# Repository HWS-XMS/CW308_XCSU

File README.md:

Requires JTAG programmer or flash connected to HDS pins to be programmed.
I am using a flash emulator on HDS, i.e. Dediprog EM100.
However, JTAG works equally well.

# Errata and plans for Rev-2:
- Use a different DC supply for VCC INT. This one provides up to 500mA. The chip can draw >500mA is specific scenarios w.r.t. the datasheet.
- Replace the three parallel shunts with my current transformer design
- Connect the SBI signals to the CW308 header, such that chipwhisperer can program (after updating chipwhisperer python, it is currently not supported)

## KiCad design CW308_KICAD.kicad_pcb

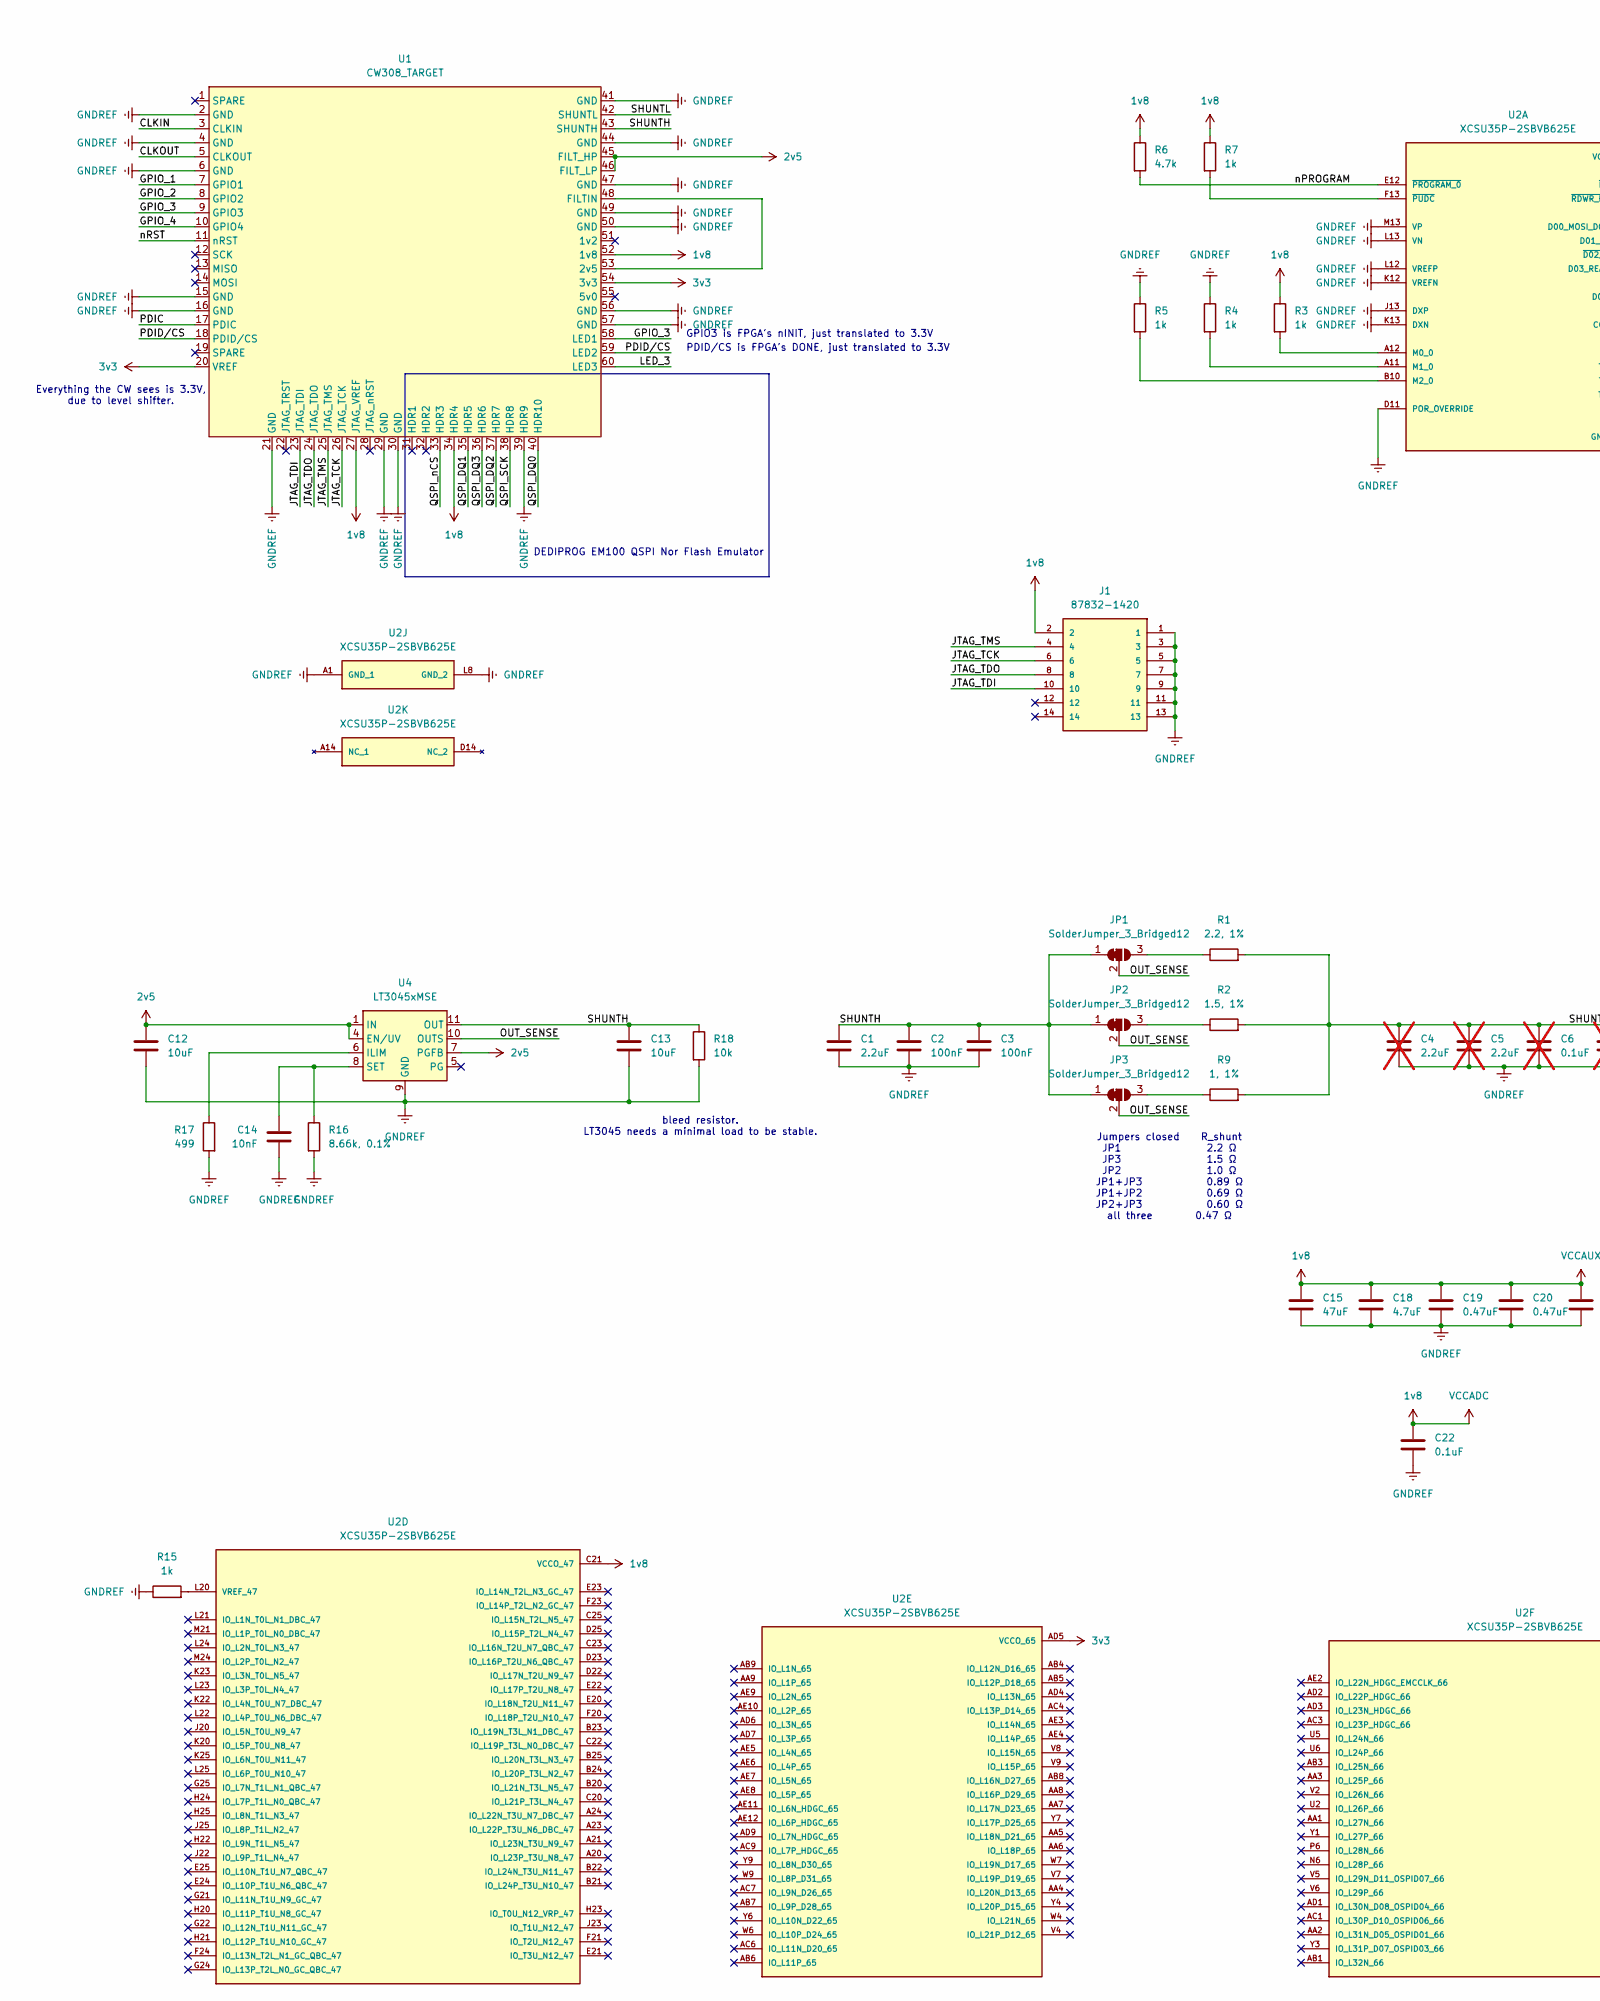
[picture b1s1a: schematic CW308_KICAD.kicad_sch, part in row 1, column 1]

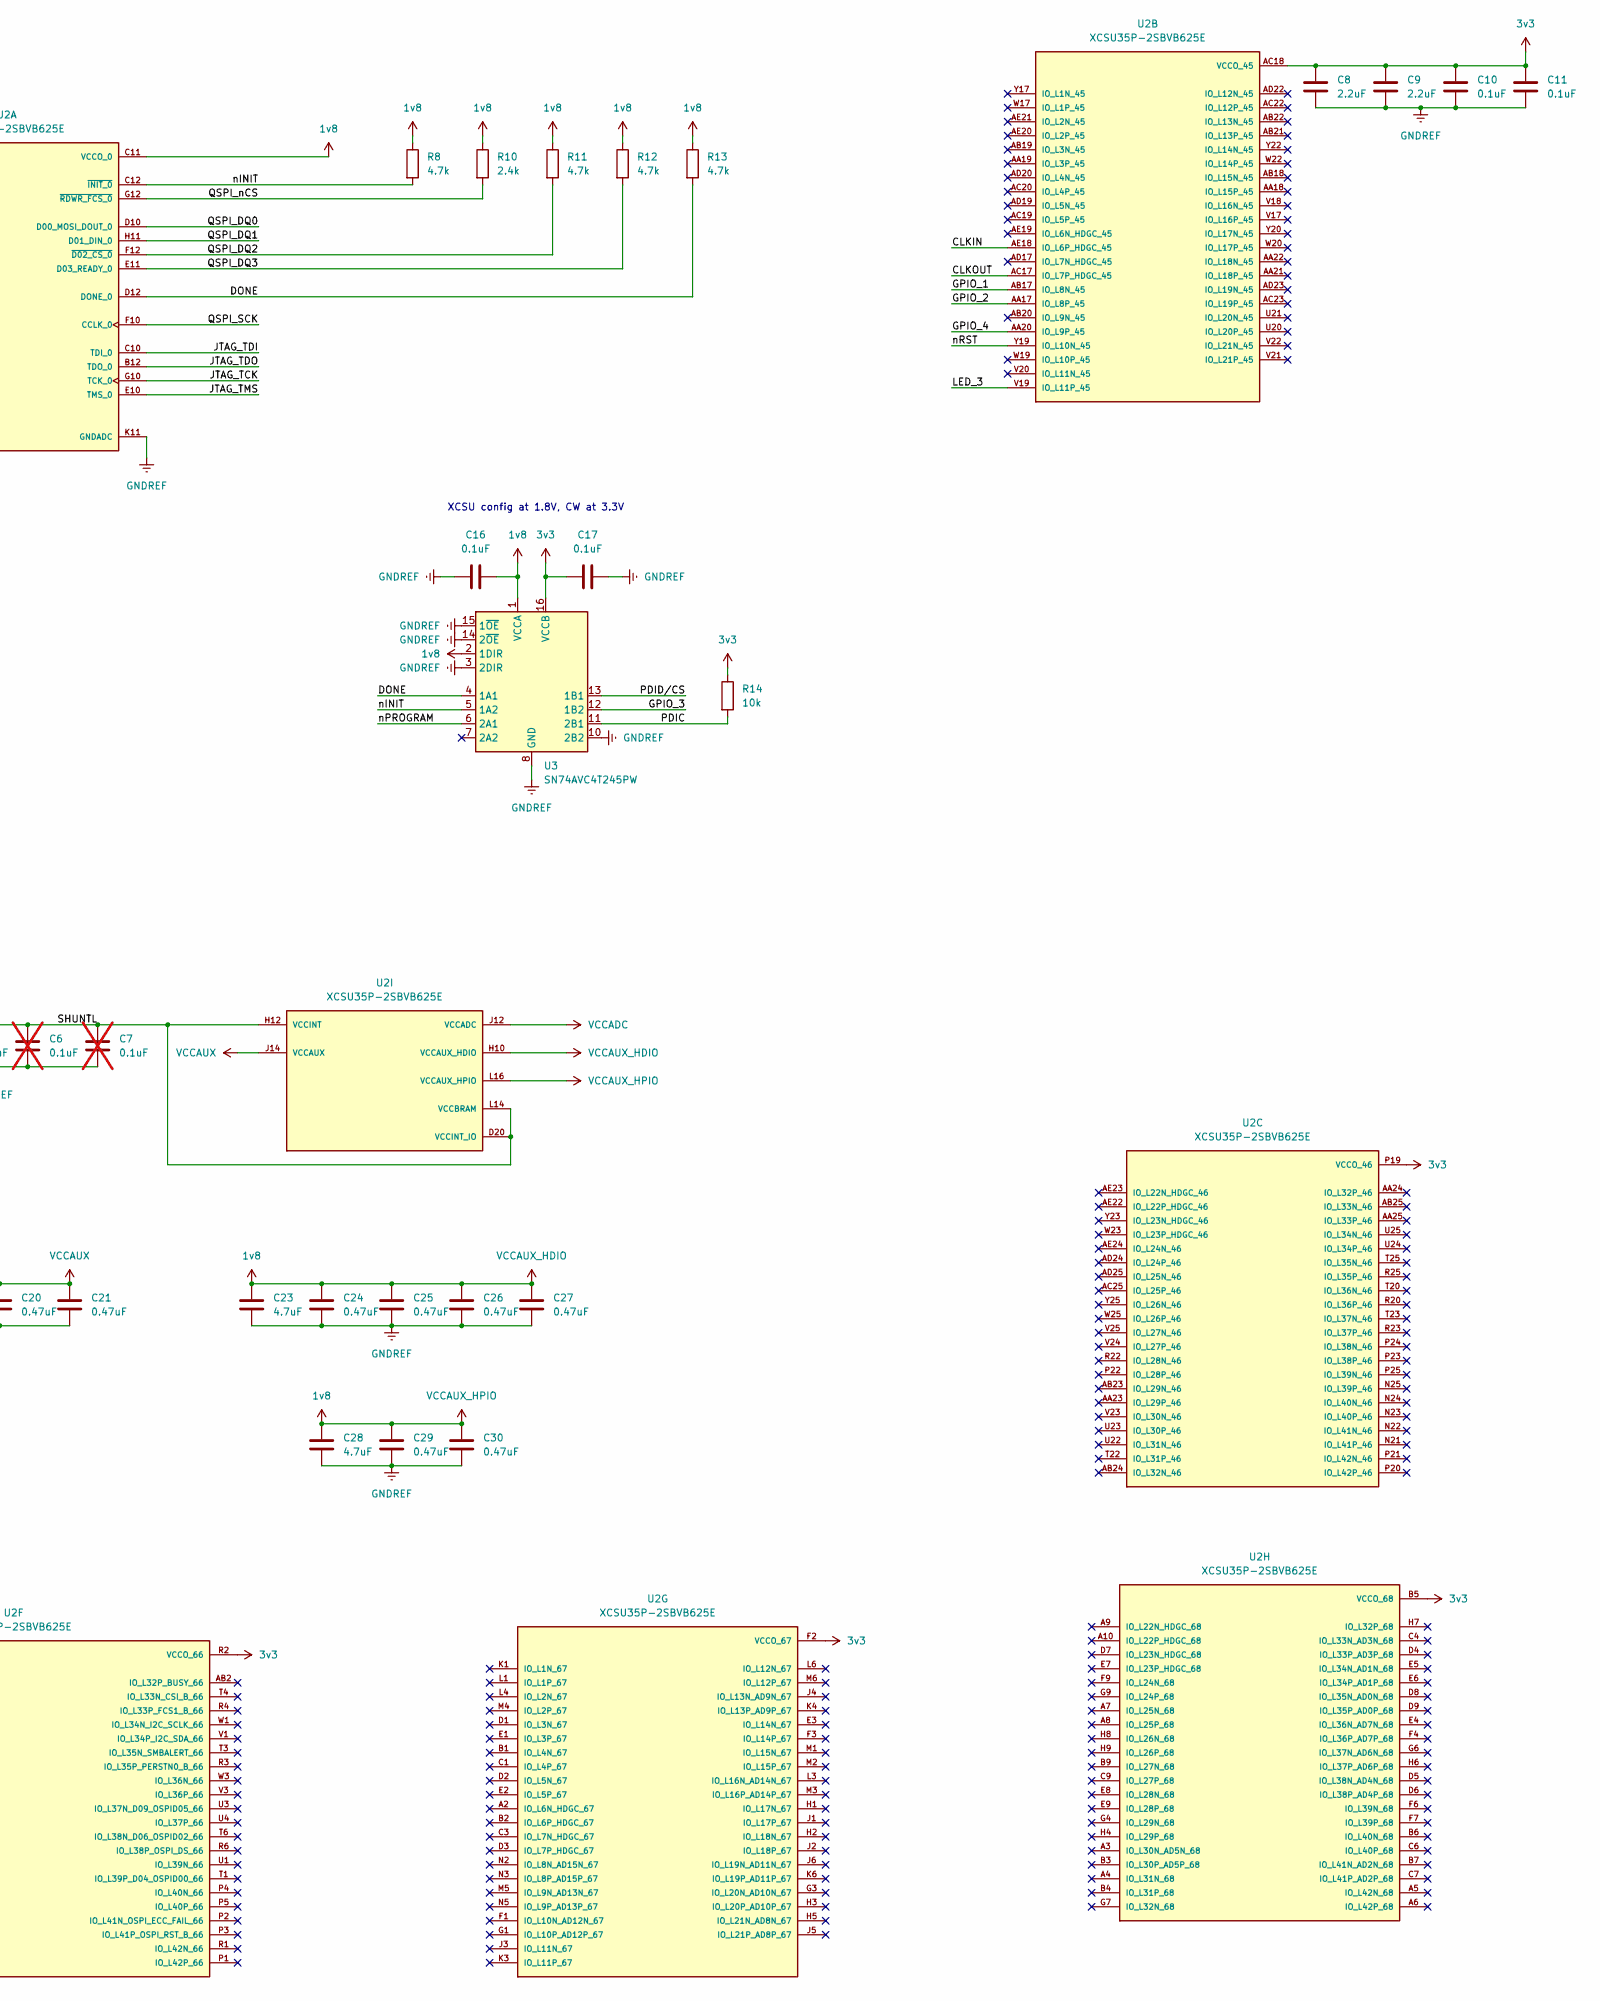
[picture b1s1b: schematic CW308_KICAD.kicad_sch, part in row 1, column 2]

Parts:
C1, C8, C9: 2.2uF; C_0603_1608Metric
C2, C3: 100nF; C_0402_1005Metric
C4, C5: 2.2uF; C_0603_1608Metric; not fitted
C6, C7: 0.1uF; C_0402_1005Metric; not fitted
C10, C11, C16, C17, C22: 0.1uF; C_0402_1005Metric
C12, C13: 10uF; C_0805_2012Metric
C14: 10nF; C_0402_1005Metric
C15: 47uF; C_1206_3216Metric
C18, C23, C28: 4.7uF; C_0603_1608Metric
C19, C20, C21, C24, C25, C26, C27, C29, C30: 0.47uF; C_0402_1005Metric
J1: 87832-1420; MOLEX_87832-1420
JP1, JP2, JP3: SolderJumper_3_Bridged12; SolderJumper-3_P1.3mm_Bridged12_RoundedPad1.0x1.5mm
R1: 2.2, 1%; R_2512_6332Metric
R2: 1.5, 1%; R_2512_6332Metric
R3, R4, R5, R7, R15: 1k; R_0402_1005Metric
R6, R8, R11, R12, R13: 4.7k; R_0402_1005Metric
R9: 1, 1%; R_2512_6332Metric
R10: 2.4k; R_0402_1005Metric
R14: 10k; R_0402_1005Metric
R16: 8.66k, 0.1%; R_0402_1005Metric
R17: 499; R_0402_1005Metric
R18: 10k; R_0805_2012Metric
U1: CW308_TARGET
U2: XCSU35P-2SBVB625E; BGA625C80P25X25_2100X2100X192; PARTREV v4.10
U3: SN74AVC4T245PW; TSSOP-16_4.4x5mm_P0.65mm
U4: LT3045xMSE; MSOP-12-1EP_3x4.039mm_P0.65mm_EP1.651x2.845mm

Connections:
1v8: C15.1, C16.2, C18.1, C19.1, C20.1, C21.1, C22.1, C23.1, C24.1, C25.1, C26.1, C27.1, C28.1, C29.1, C30.1, J1.2, R3.1, R6.1, R7.1, R8.1, R10.1, R11.1, R12.1, R13.1, U1.27 (JTAG_VREF), U1.34 (HDR4), U1.52 (1v8), U2.C11 (VCCO_0), U2.C21 (VCCO_47), U2.D24 (VCCO_47), U2.G11 (VCCO_0), U2.H10 (VCCAUX_HDIO), U2.J10 (VCCAUX_HDIO), U2.J12 (VCCADC), U2.J14 (VCCAUX), U2.J17 (VCCAUX_HDIO), U2.J18 (VCCAUX_HDIO), U2.K8 (VCCAUX_HDIO), U2.K9 (VCCAUX_HDIO), U2.K21 (VCCO_47), U2.K24 (VCCO_47), U2.L16 (VCCAUX_HPIO), U2.L18 (VCCO_47), U2.M11 (VCCAUX), U2.M19 (VCCAUX_HPIO), U2.M22 (VCCAUX_HPIO), U2.N7 (VCCAUX_HDIO), U2.N11 (VCCAUX), U2.N12 (VCCO_0), U2.N14 (VCCAUX), U2.N16 (VCCAUX_HDIO), U2.N18 (VCCAUX_HDIO), U2.N20 (VCCAUX_HPIO), U2.P15 (VCCAUX), U2.R11 (VCCAUX), U2.R14 (VCCAUX), U2.R18 (VCCAUX_HDIO), U2.T8 (VCCAUX_HDIO), U2.T9 (VCCAUX_HDIO), U2.T15 (VCCAUX), U2.T18 (VCCAUX_HDIO), U2.U10 (VCCAUX_HDIO), U2.U16 (VCCAUX_HDIO), U2.U17 (VCCAUX_HDIO), U3.1 (VCCA), U3.2 (1DIR)
2v5: C12.1, U1.45 (FILT_HP), U1.46 (FILT_LP), U4.1 (IN), U4.2 (IN), U4.3 (IN), U4.4 (EN/UV), U4.7 (PGFB)
3v3: C8.2, C9.2, C10.2, C11.2, C17.1, R14.1, U1.20 (VREF), U1.54 (3v3), U2.AC18 (VCCO_45), U2.AC21 (VCCO_45), U2.AD5 (VCCO_65), U2.AD8 (VCCO_65), U2.B5 (VCCO_68), U2.C8 (VCCO_68), U2.F2 (VCCO_67), U2.F5 (VCCO_68), U2.G8 (VCCO_68), U2.J8 (VCCO_68), U2.K7 (VCCO_67), U2.L2 (VCCO_67), U2.L5 (VCCO_67), U2.L7 (VCCO_67), U2.P19 (VCCO_46), U2.R2 (VCCO_66), U2.R5 (VCCO_66), U2.R7 (VCCO_66), U2.R19 (VCCO_46), U2.R21 (VCCO_46), U2.T7 (VCCO_66), U2.T24 (VCCO_46), U2.U8 (VCCO_65), U2.U19 (VCCO_45), U2.W2 (VCCO_66), U2.W8 (VCCO_65), U2.W18 (VCCO_45), U2.W21 (VCCO_45), U2.Y5 (VCCO_65), U2.Y24 (VCCO_46), U3.16 (VCCB)
/CLKIN: U1.3 (CLKIN), U2.AE18 (IO_L6P_HDGC_45)
/CLKOUT: U1.5 (CLKOUT), U2.AC17 (IO_L7P_HDGC_45)
/DONE: R13.2, U2.D12 (DONE_0), U3.4 (1A1)
/GPIO_1: U1.7 (GPIO1), U2.AB17 (IO_L8N_45)
/GPIO_2: U1.8 (GPIO2), U2.AA17 (IO_L8P_45)
/GPIO_3: U1.9 (GPIO3), U1.58 (LED1), U3.12 (1B2)
/GPIO_4: U1.10 (GPIO4), U2.AA20 (IO_L9P_45)
/JTAG_TCK: J1.6, U1.26 (JTAG_TCK), U2.G10 (TCK_0)
/JTAG_TDI: J1.10, U1.23 (JTAG_TDI), U2.C10 (TDI_0)
/JTAG_TDO: J1.8, U1.24 (JTAG_TDO), U2.B12 (TDO_0)
/JTAG_TMS: J1.4, U1.25 (JTAG_TMS), U2.E10 (TMS_0)
/LED_3: U1.60 (LED3), U2.V19 (IO_L11P_45)
/OUT_SENSE: JP1.2 (C), JP2.2 (C), JP3.2 (C), U4.10 (OUTS)
/PDIC: R14.2, U1.17 (PDIC), U3.11 (2B1)
/PDID/CS: U1.18 (PDID/CS), U1.59 (LED2), U3.13 (1B1)
/QSPI_DQ0: U1.40 (HDR10), U2.D10 (D00_MOSI_DOUT_0)
/QSPI_DQ1: U1.35 (HDR5), U2.H11 (D01_DIN_0)
/QSPI_DQ2: R11.2, U1.37 (HDR7), U2.F12 (~D02_CS_0)
/QSPI_DQ3: R12.2, U1.36 (HDR6), U2.E11 (D03_READY_0)
/QSPI_SCK: U1.38 (HDR8), U2.F10 (CCLK_0)
/QSPI_nCS: R10.2, U1.33 (HDR3), U2.G12 (~RDWR_FCS_0)
/SHUNTH: C1.1, C2.1, C3.1, C13.1, JP1.1 (A), JP2.1 (A), JP3.1 (A), R18.1, U1.43 (SHUNTH), U4.11 (OUT), U4.12 (OUT)
/nINIT: R8.2, U2.C12 (~INIT_0), U3.5 (1A2)
/nPROGRAM: R6.2, U2.E12 (~PROGRAM_0), U3.6 (2A1)
/nRST: U1.11 (nRST), U2.Y19 (IO_L10N_45)
GNDREF: C1.2, C2.2, C3.2, C4.2, C5.2, C6.2, C7.2, C8.1, C9.1, C10.1, C11.1, C12.2, C13.2, C14.2, C15.2, C16.1, C17.2, C18.2, C19.2, C20.2, C21.2, C22.2, C23.2, C24.2, C25.2, C26.2, C27.2, C28.2, C29.2, C30.2, J1.1, J1.3, J1.5, J1.7, J1.9, J1.11, J1.13, R4.1, R5.1, R15.1, R16.2, R17.2, R18.2, U1.2 (GND), U1.4 (GND), U1.6 (GND), U1.15 (GND), U1.16 (GND), U1.21 (GND), U1.29 (GND), U1.30 (GND), U1.39 (HDR9), U1.41 (GND), U1.44 (GND), U1.47 (GND), U1.49 (GND), U1.50 (GND), U1.56 (GND), U1.57 (GND), U2.A1 (GND_1), U2.A13 (GND_1), U2.A22 (GND_1), U2.A25 (GND_1), U2.AB13 (GND_1), U2.AC2 (GND_1), U2.AC5 (GND_1), U2.AC8 (GND_1), U2.AC24 (GND_1), U2.AD11 (GND_1), U2.AD15 (GND_1), U2.AD18 (GND_1), U2.AD21 (GND_1), U2.AE1 (GND_1), U2.AE13 (GND_1), U2.AE25 (GND_1), U2.B8 (GND_1), U2.B11 (GND_1), U2.B15 (GND_1), U2.B18 (GND_1), U2.C2 (GND_1), U2.C5 (GND_1), U2.C24 (GND_1), U2.D11 (POR_OVERRIDE), U2.D13 (GND_1), U2.D21 (GND_1), U2.F8 (GND_1), U2.F11 (GND_1), U2.F15 (GND_1), U2.F18 (GND_1), U2.F22 (GND_1), U2.F25 (GND_1), U2.G2 (GND_1), U2.G5 (GND_1), U2.G13 (GND_1), U2.G20 (GND_1), U2.G23 (GND_1), U2.J7 (GND_1), U2.J9 (GND_1), U2.J13 (DXP), U2.J16 (GND_1), U2.J19 (GND_1), U2.J21 (GND_1), U2.J24 (GND_1), U2.K2 (GND_1), U2.K5 (GND_1), U2.K10 (GND_1), U2.K11 (GNDADC), U2.K12 (VREFN), U2.K13 (DXN), U2.K15 (GND_1), U2.K18 (GND_1), U2.L8 (GND_2), U2.L11 (GND_1), U2.L12 (VREFP), U2.L13 (VN), U2.L15 (GND_1), U2.L17 (GND_1), U2.L19 (GND_2), U2.M7 (GND_2), U2.M9 (GND_2), U2.M13 (VP), U2.M14 (GND_2), U2.M16 (GND_2), U2.M20 (GND_2), U2.M23 (GND_2), U2.M25 (GND_2), U2.N1 (GND_2), U2.N4 (GND_2), U2.N8 (GND_2), U2.N10 (GND_2), U2.N13 (GND_2), U2.N15 (GND_2), U2.N17 (GND_2), U2.N19 (GND_2), U2.P7 (GND_2), U2.P9 (GND_2), U2.P11 (GND_2), U2.P12 (GND_2), U2.P14 (GND_2), U2.P16 (GND_2), U2.P18 (GND_2), U2.R8 (GND_2), U2.R10 (GND_2), U2.R13 (GND_2), U2.R15 (GND_2), U2.R17 (GND_2), U2.R24 (GND_2), U2.T2 (GND_2), U2.T5 (GND_2), U2.T11 (GND_2), U2.T14 (GND_2), U2.T16 (GND_2), U2.T19 (GND_2), U2.T21 (GND_2), U2.U7 (GND_2), U2.U9 (GND_2), U2.U12 (GND_2), U2.U18 (GND_2), U2.W5 (GND_2), U2.W13 (GND_2), U2.W24 (GND_2), U2.Y2 (GND_2), U2.Y8 (GND_2), U2.Y11 (GND_2), U2.Y15 (GND_2), U2.Y18 (GND_2), U2.Y21 (GND_2), U3.3 (2DIR), U3.8 (GND), U3.9 (GND), U3.10 (2B2), U3.14 (2~OE), U3.15 (1~OE), U4.9 (GND), U4.13 (GND)
unnamed: JP1.3 (B), R1.1
unnamed: JP2.3 (B), R2.1
unnamed: JP3.3 (B), R9.1
unnamed: U1.48 (FILTIN), U1.53 (2v5)
unnamed: R3.2, U2.A12 (M0_0)
unnamed: R4.2, U2.A11 (M1_0)
unnamed: R5.2, U2.B10 (M2_0)
unnamed: R7.2, U2.F13 (~PUDC)
unnamed: R15.2, U2.L20 (VREF_47)
unnamed: R17.1, U4.6 (ILIM)
unnamed: C14.1, R16.1, U4.8 (SET)
VCCBRAM: C4.1, C5.1, C6.1, C7.1, R1.2, R2.2, R9.2, U1.42 (SHUNTL), U2.D20 (VCCINT_IO), U2.H12 (VCCINT), U2.H13 (VCCINT), U2.J11 (VCCINT), U2.K14 (VCCINT), U2.K16 (VCCINT_IO), U2.K17 (VCCINT_IO), U2.K19 (VCCINT_IO), U2.L9 (VCCINT), U2.L10 (VCCINT), U2.L14 (VCCBRAM), U2.M8 (VCCINT), U2.M10 (VCCINT), U2.M12 (VCCINT), U2.M15 (VCCINT), U2.M17 (VCCINT), U2.M18 (VCCINT), U2.N9 (VCCINT), U2.P8 (VCCINT), U2.P10 (VCCINT), U2.P13 (VCCBRAM), U2.P17 (VCCINT), U2.R9 (VCCINT), U2.R12 (VCCBRAM), U2.R16 (VCCINT), U2.T10 (VCCINT), U2.T12 (VCCINT), U2.T13 (VCCBRAM), U2.T17 (VCCINT), U2.U11 (VCCINT), U2.U13 (VCCBRAM), U2.U14 (VCCINT), U2.U15 (VCCINT), U2.V13 (VCCINT)

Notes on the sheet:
XCSU config at 1.8V, CW at 3.3V
DEDIPROG EM100 QSPI Nor Flash Emulator
Jumpers closed R_shunt JP1 2.2 Ω JP3 1.5 Ω JP2 1.0 Ω JP1+JP3 0.89 Ω JP1+JP2 0.69 Ω JP2+JP3 0.60 Ω all three 0.47 Ω
Everything the CW sees is 3.3V, due to level shifter.
GPIO3 is FPGA's nINIT, just translated to 3.3V
bleed resistor. LT3045 needs a minimal load to be stable.
PDID/CS is FPGA's DONE, just translated to 3.3V

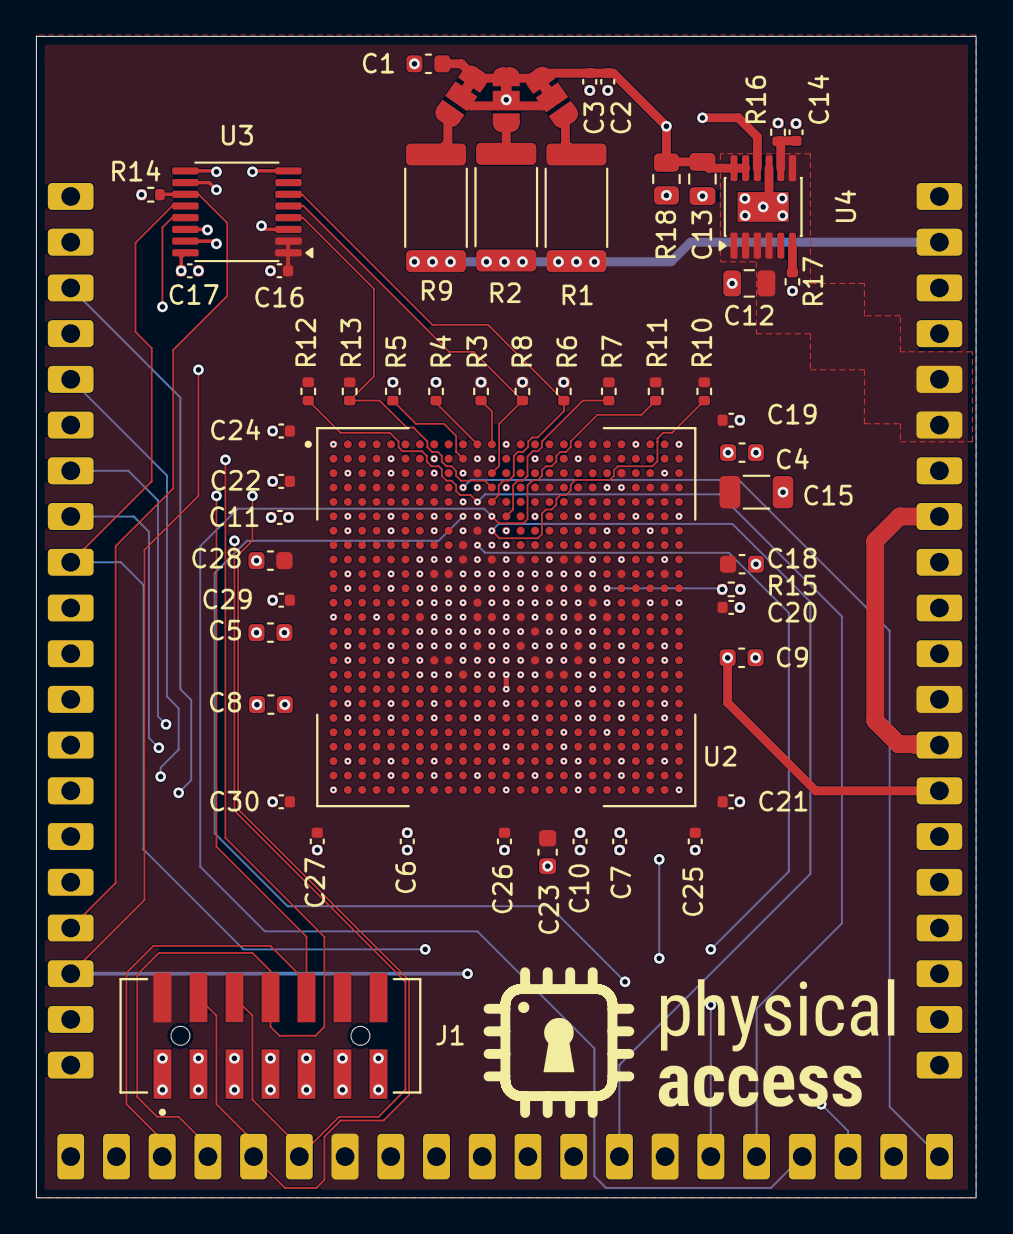
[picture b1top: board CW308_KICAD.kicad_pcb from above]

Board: 4 copper layers, 52.2 x 64.5 mm, 56 parts (0 on the bottom side), 41 nets.

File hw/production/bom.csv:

Designator,Footprint,Quantity,Value,LCSC Part #
"C1, C4, C5, C8, C9",0603,5,2.2uF,
"C10, C11, C16, C17, C22, C6, C7",0402,7,0.1uF,
"C12, C13",0805,2,10uF,
C14,0402,1,10nF,
C15,1206,1,47uF,
"C18, C23, C28",0603,3,4.7uF,
"C19, C20, C21, C24, C25, C26, C27, C29, C30",0402,9,0.47uF,
"C2, C3",0402,2,100nF,
J1,MOLEX_87832-1420,1,87832-1420,
R1,2512,1,"2.2, 1%",
R10,0402,1,2.4k,
"R11, R12, R13, R6, R8",0402,5,4.7k,
R14,0402,1,10k,
"R15, R3, R4, R5, R7",0402,5,1k,
R16,0402,1,"8.66k, 0.1%",
R17,0402,1,499,
R18,0805,1,10k,
R2,2512,1,"1.5, 1%",
R9,2512,1,"1, 1%",
U1,CW308_TARGET,1,CW308_TARGET,
U2,BGA625C80P25X25_2100X2100X192,1,XCSU35P-2SBVB625E,
U3,TSSOP-16_4.4x5mm_P0.65mm,1,SN74AVC4T245PW,
U4,MSOP-12-1EP_3x4.039mm_P0.65mm_EP1.651x2.845mm,1,LT3045xMSE,

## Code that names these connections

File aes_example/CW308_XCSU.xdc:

set_property PACKAGE_PIN AE18     [get_ports clkin]
set_property IOSTANDARD  LVCMOS33 [get_ports clkin]
set_property PACKAGE_PIN AC17     [get_ports clkout]
set_property IOSTANDARD  LVCMOS33 [get_ports clkout]
create_clock -name clkin -period 100.000 -waveform {0.000 50.000} [get_ports clkin]

set_property PACKAGE_PIN AB17     [get_ports gpio1]
set_property IOSTANDARD  LVCMOS33 [get_ports gpio1]
set_property PACKAGE_PIN AA17     [get_ports gpio2]
set_property IOSTANDARD  LVCMOS33 [get_ports gpio2]
set_property PACKAGE_PIN AA20     [get_ports gpio4]
set_property IOSTANDARD  LVCMOS33 [get_ports gpio4]
set_property PACKAGE_PIN Y19      [get_ports nrst]
set_property IOSTANDARD  LVCMOS33 [get_ports nrst]

set_property PACKAGE_PIN V19      [get_ports led3]
set_property IOSTANDARD  LVCMOS33 [get_ports led3]

set_property CONFIG_MODE SPIx4                     [current_design]
set_property BITSTREAM.CONFIG.UNUSEDPIN PULLNONE   [current_design]
